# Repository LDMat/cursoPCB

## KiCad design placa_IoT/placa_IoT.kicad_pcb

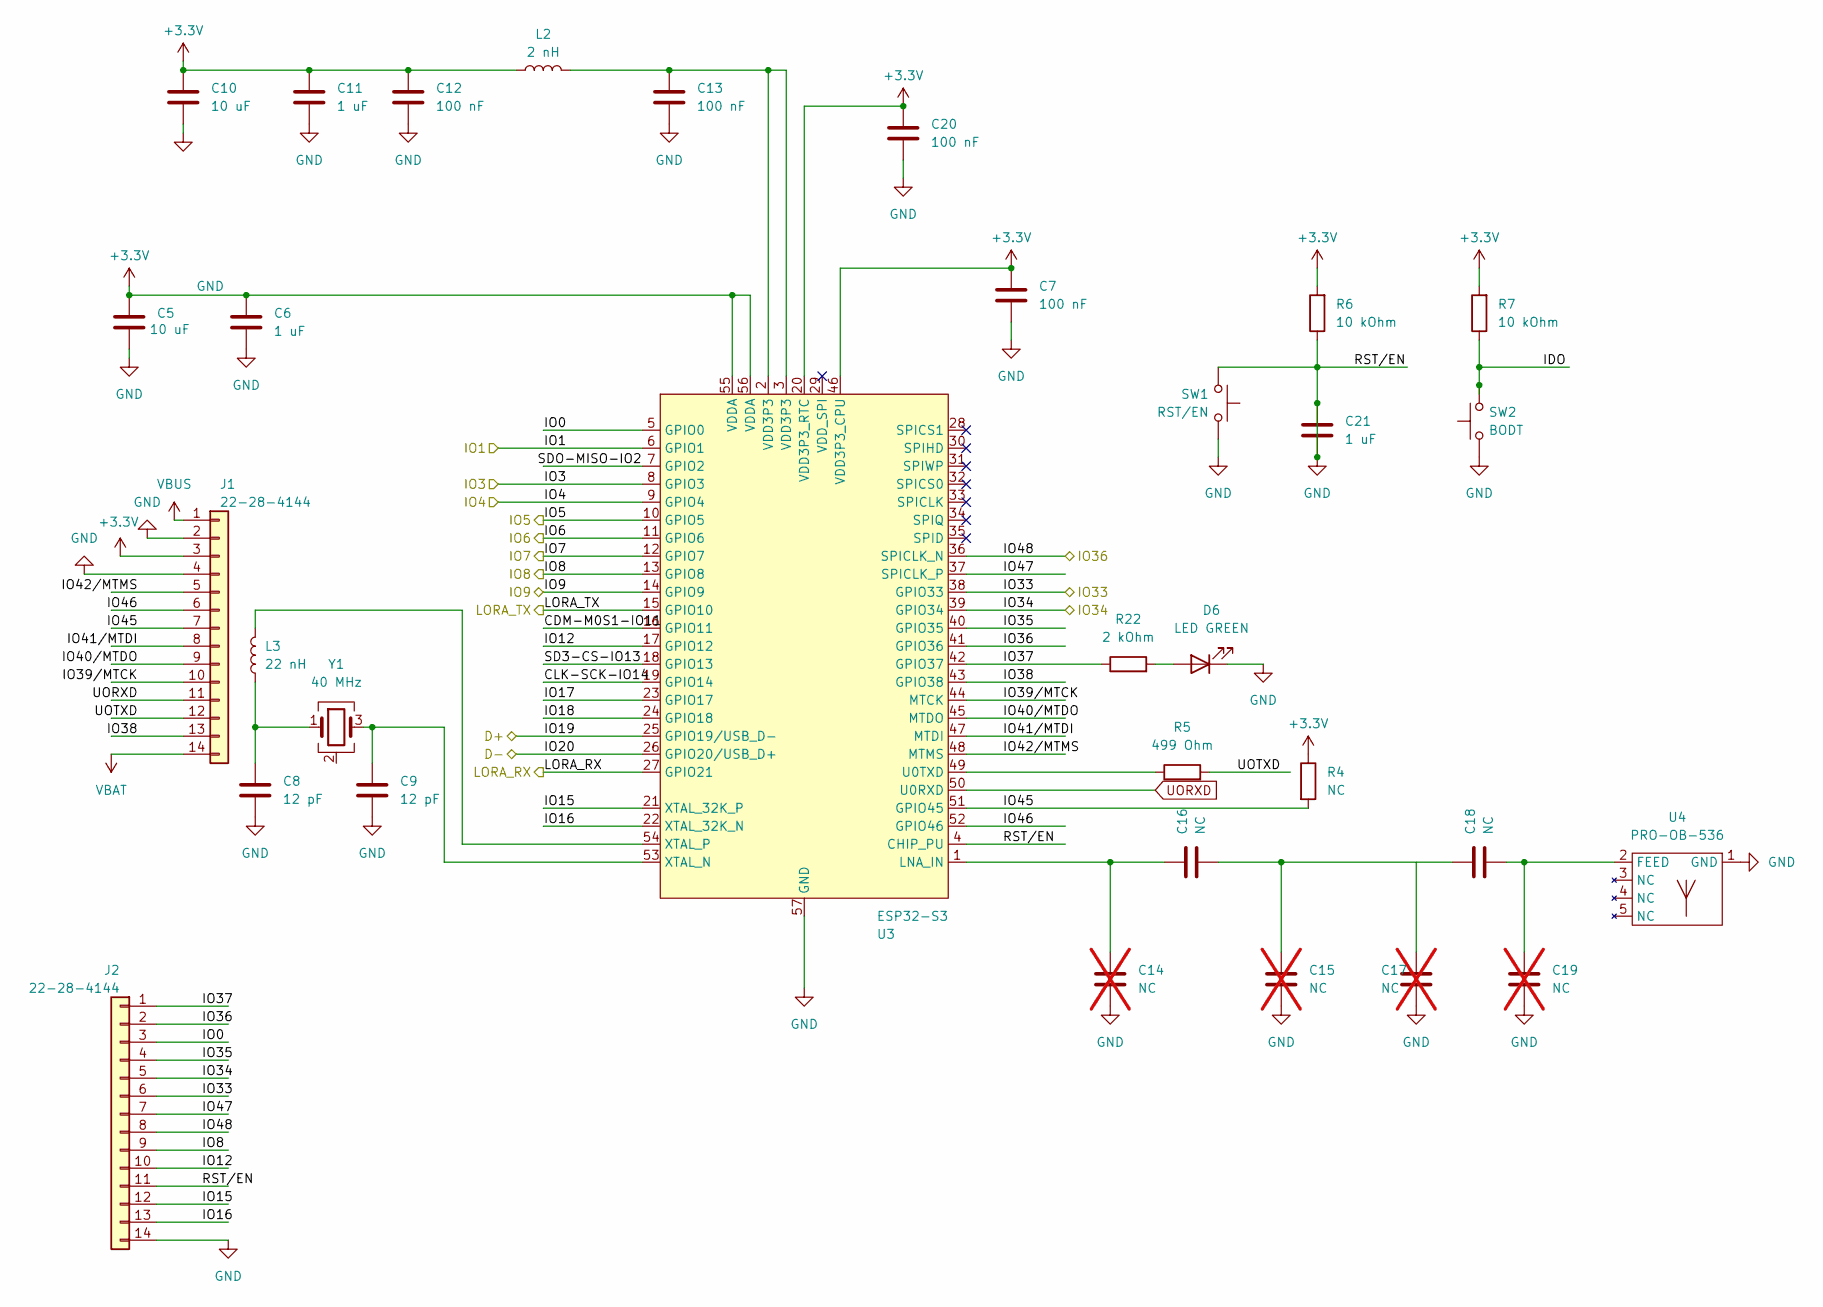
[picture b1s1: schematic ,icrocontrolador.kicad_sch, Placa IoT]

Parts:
C5, C10: 10 uF; C_0402_1005Metric
C6, C11, C21: 1 uF; C_0402_1005Metric
C7, C12, C13, C20: 100 nF; C_0402_1005Metric
C8, C9: 12 pF; C_0402_1005Metric
C14, C15, C17, C19: NC; C_0402_1005Metric; not fitted
C16, C18: NC; C_0402_1005Metric
D6: LED GREEN; LED_0402_1005Metric
J1, J2: 22-28-4144; CONN_THT_MV_PH_P2.54MM_P14
L2: 2 nH; L_0402_1005Metric
L3: 22 nH; L_0402_1005Metric
R4: NC; R_0402_1005Metric
R5: 499 Ohm; R_0402_1005Metric
R6, R7: 10 kOhm; R_0402_1005Metric
R22: 2 kOhm; R_0402_1005Metric
SW1: RST/EN; SW_Push_SPST_NO_Alps_SKRK
SW2: BODT; SW_Push_SPST_NO_Alps_SKRK
U3: ESP32-S3; QFN-56-1EP_7x7mm_P0.4mm_EP4x4mm
U4: PRO-OB-536; ANTENNA_PIFA_3D_2.4GHZ
Y1: 40 MHz; Crystal_SMD_3225-4Pin_3.2x2.5mm

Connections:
+3.3V: C5.1, C6.1, C7.1, C10.1, C11.1, C12.1, C20.1, J1.3, L2.1, R4.1, R6.2, R7.2, U3.20 (VDD3P3_RTC), U3.46 (VDD3P3_CPU), U3.55 (VDDA), U3.56 (VDDA); also elsewhere on the board
/MICROCONTROLADOR/CDM-M0S1-IO11: U3.16 (GPIO11)
/MICROCONTROLADOR/CLK-SCK-IO14: U3.19 (GPIO14)
/MICROCONTROLADOR/IDO: R7.1, SW2.2
/MICROCONTROLADOR/IO0: J2.3, U3.5 (GPIO0)
/MICROCONTROLADOR/IO1: U3.6 (GPIO1); also elsewhere on the board
/MICROCONTROLADOR/IO3: U3.8 (GPIO3); also elsewhere on the board
/MICROCONTROLADOR/IO4: U3.9 (GPIO4); also elsewhere on the board
/MICROCONTROLADOR/IO5: U3.10 (GPIO5); also elsewhere on the board
/MICROCONTROLADOR/IO6: U3.11 (GPIO6); also elsewhere on the board
/MICROCONTROLADOR/IO7: U3.12 (GPIO7)
/MICROCONTROLADOR/IO8: J2.9, U3.13 (GPIO8); also elsewhere on the board
/MICROCONTROLADOR/IO12: J2.10, U3.17 (GPIO12)
/MICROCONTROLADOR/IO15: J2.12, U3.21 (XTAL_32K_P)
/MICROCONTROLADOR/IO16: J2.13, U3.22 (XTAL_32K_N)
/MICROCONTROLADOR/IO17: U3.23 (GPIO17)
/MICROCONTROLADOR/IO18: U3.24 (GPIO18)
/MICROCONTROLADOR/IO19: U3.25 (GPIO19/USB_D-), U3.26 (GPIO20/USB_D+); also elsewhere on the board
/MICROCONTROLADOR/IO33: J2.6, U3.14 (GPIO9), U3.15 (GPIO10), U3.27 (GPIO21), U3.38 (GPIO33); also elsewhere on the board
/MICROCONTROLADOR/IO34: J2.5, U3.39 (GPIO34); also elsewhere on the board
/MICROCONTROLADOR/IO35: J2.4, U3.40 (GPIO35)
/MICROCONTROLADOR/IO36: J2.2, J2.8, U3.36 (SPICLK_N), U3.41 (GPIO36); also elsewhere on the board
/MICROCONTROLADOR/IO37: J2.1, R22.1, U3.42 (GPIO37)
/MICROCONTROLADOR/IO38: J1.13, U3.43 (GPIO38)
/MICROCONTROLADOR/IO39/MTCK: J1.10, U3.44 (MTCK)
/MICROCONTROLADOR/IO40/MTDO: J1.9, U3.45 (MTDO)
/MICROCONTROLADOR/IO41/MTDI: J1.8, U3.47 (MTDI)
/MICROCONTROLADOR/IO42/MTMS: J1.5, U3.48 (MTMS)
/MICROCONTROLADOR/IO45: J1.7, R4.2, U3.51 (GPIO45)
/MICROCONTROLADOR/IO46: J1.6, U3.52 (GPIO46)
/MICROCONTROLADOR/IO47: J2.7, U3.37 (SPICLK_P)
/MICROCONTROLADOR/SD3-CS-IO13: U3.18 (GPIO13)
/MICROCONTROLADOR/SDO-MISO-IO2: U3.7 (GPIO2)
/MICROCONTROLADOR/UOTXD: J1.12, R5.2
GND: C5.2, C6.2, C7.2, C8.2, C9.2, C10.2, C11.2, C12.2, C13.2, C14.1, C15.1, C17.1, C19.1, C20.2, C21.1, C21.2, D6.1 (K), J1.2, J1.4, J2.11, J2.14, R6.1, SW1.1, SW1.2, SW2.1, U3.4 (CHIP_PU), U3.57 (GND), U4.1 (GND); also elsewhere on the board
unnamed: C8.1, L3.1, Y1.1
unnamed: C13.1, L2.2, U3.2 (VDD3P3), U3.3 (VDD3P3)
unnamed: C15.2, C16.1, C18.2
unnamed: D6.2 (A), R22.2
unnamed: C14.2, C16.2, U3.1 (LNA_IN)
unnamed: R5.1, U3.49 (U0TXD)
unnamed: C9.1, U3.53 (XTAL_N), Y1.3
unnamed: L3.2, U3.54 (XTAL_P)
unnamed: C18.1, C19.2, U4.2 (FEED)
unnamed: Y1.2 (G), Y1.4 (G)
UORXD: J1.11, U3.50 (U0RXD)
VBAT: J1.14; also elsewhere on the board
VBUS: J1.1; also elsewhere on the board

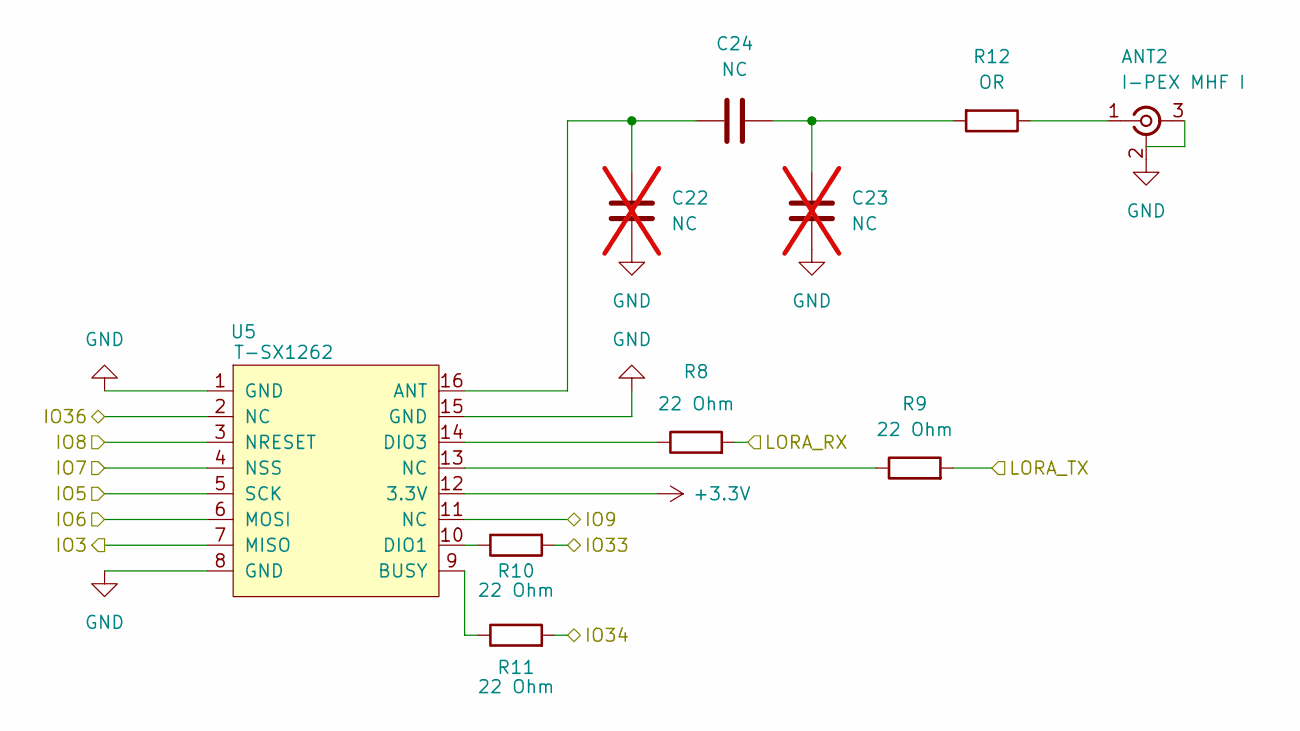
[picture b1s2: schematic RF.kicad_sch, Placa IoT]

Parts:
ANT2: I-PEX MHF I; IPEX_MHF_I
C22, C23: NC; C_0402_1005Metric; not fitted
C24: NC; C_0402_1005Metric
R8, R9, R10, R11: 22 Ohm; R_0402_1005Metric
R12: OR; R_0402_1005Metric
U5: T-SX1262; MODULE_T_SX1262

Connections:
+3.3V: U5.12 (3.3V); also elsewhere on the board
/MICROCONTROLADOR/IO3: U5.7 (MISO); also elsewhere on the board
/MICROCONTROLADOR/IO5: U5.5 (SCK); also elsewhere on the board
/MICROCONTROLADOR/IO6: U5.6 (MOSI); also elsewhere on the board
/MICROCONTROLADOR/IO8: U5.3 (NRESET); also elsewhere on the board
/MICROCONTROLADOR/IO33: R8.2, R9.2, R10.2, U5.11 (NC); also elsewhere on the board
/MICROCONTROLADOR/IO34: R11.2; also elsewhere on the board
/MICROCONTROLADOR/IO36: U5.2 (NC); also elsewhere on the board
/RF/IO7: U5.4 (NSS)
GND: ANT2.2 (Ext), C22.1, C23.1, U5.1 (GND), U5.8 (GND), U5.15 (GND); also elsewhere on the board
unnamed: ANT2.1 (In), R12.1
unnamed: C23.2, C24.1, R12.2
unnamed: R9.1, U5.13 (NC)
unnamed: C22.2, C24.2, U5.16 (ANT)
unnamed: R11.1, U5.9 (BUSY)
unnamed: R10.1, U5.10 (DIO1)
unnamed: R8.1, U5.14 (DIO3)

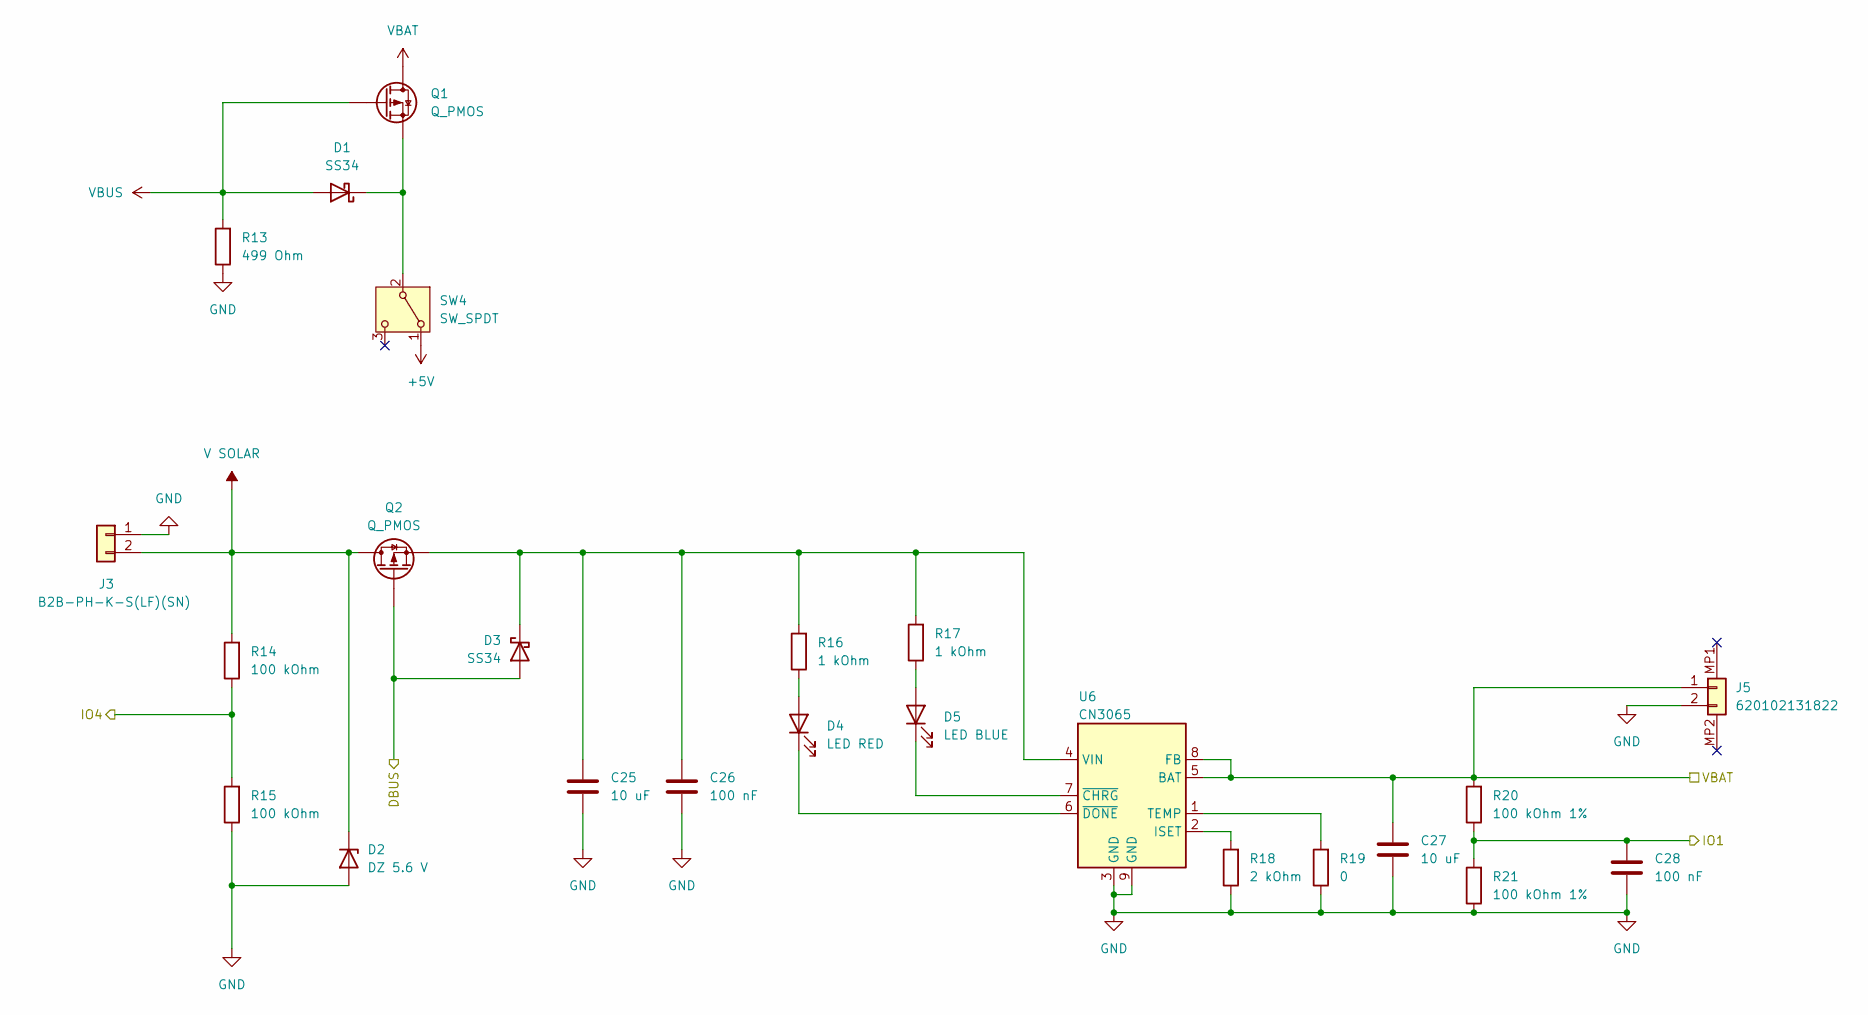
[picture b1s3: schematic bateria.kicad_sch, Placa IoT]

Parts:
C25, C27: 10 uF; C_0402_1005Metric
C26, C28: 100 nF; C_0402_1005Metric
D1, D3: SS34; D_SMA
D2: DZ 5.6 V; D_SOD-123
D4: LED RED; LED_0402_1005Metric
D5: LED BLUE; LED_0402_1005Metric
J3: B2B-PH-K-S(LF)(SN); CONN_THT_MV_JST_P2.00MM_P2
J5: 620102131822; CONN_SMT_MH_SH_P2.00MM_P2
Q1, Q2: Q_PMOS; SOT-23
R13: 499 Ohm; R_0402_1005Metric
R14, R15: 100 kOhm; R_0402_1005Metric
R16, R17: 1 kOhm; R_0402_1005Metric
R18: 2 kOhm; R_0402_1005Metric
R19: 0; R_0402_1005Metric
R20, R21: 100 kOhm 1%; R_0402_1005Metric
SW4: SW_SPDT; SW_Slide_SPDT_Angled_CK_OS102011MA1Q
U6: CN3065; DFN-8-1EP_3x3mm_P0.5mm_EP1.66x2.38mm

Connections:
+5V: SW4.1 (A); also elsewhere on the board
/BATERIA/DBUS: D3.2 (A), Q2.1 (G)
/MICROCONTROLADOR/IO1: C28.1, R20.1, R21.2; also elsewhere on the board
/MICROCONTROLADOR/IO4: R14.1, R15.2; also elsewhere on the board
GND: C25.2, C26.2, C27.2, C28.2, D2.2 (A), J3.1, J5.2, R13.1, R15.1, R18.1, R19.1, R21.1, U6.3 (GND), U6.9 (GND); also elsewhere on the board
unnamed: D1.1 (K), Q1.2 (S), SW4.2 (B)
unnamed: C25.1, C26.1, D3.1 (K), Q2.2 (S), R16.2, R17.2, U6.4 (VIN)
unnamed: D4.2 (A), R16.1
unnamed: D4.1 (K), U6.6 (~DONE)
unnamed: D5.2 (A), R17.1
unnamed: D5.1 (K), U6.7 (~CHRG)
unnamed: R18.2, U6.2 (ISET)
unnamed: R19.2, U6.1 (TEMP)
V SOLAR: D2.1 (K), J3.2, Q2.3 (D), R14.2
VBAT: C27.1, J5.1, Q1.3 (D), R20.2, U6.5 (BAT), U6.8 (FB); also elsewhere on the board
VBUS: D1.2 (A), Q1.1 (G), R13.2; also elsewhere on the board

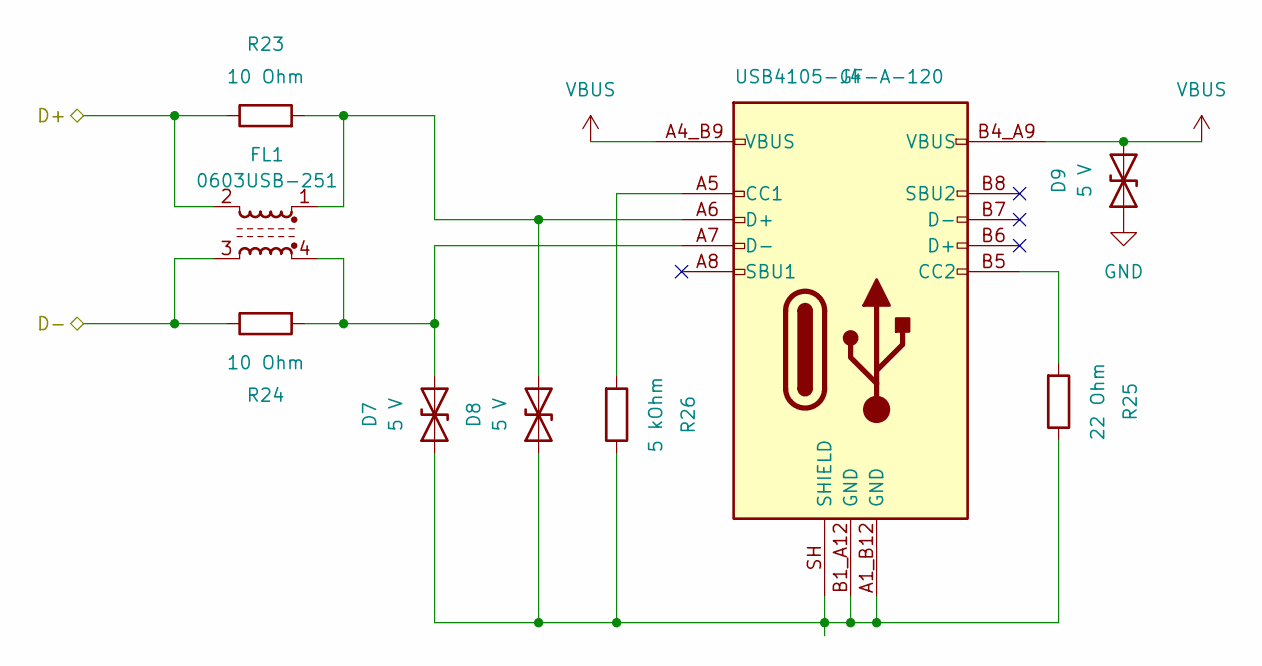
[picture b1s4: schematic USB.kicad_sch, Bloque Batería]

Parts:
D7, D8, D9: 5 V; D_SOD-882
FL1: 0603USB-251; L_CommonModeChoke_Coilcraft_0603USB
J4: USB4105-GF-A-120; CONN_SMT_RH_USBC_P0.50MM_P16
R23, R24: 10 Ohm; R_0402_1005Metric
R25: 22 Ohm; R_0402_1005Metric
R26: 5 kOhm; R_0402_1005Metric

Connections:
/MICROCONTROLADOR/IO19: FL1.2, FL1.3, R23.1, R24.1; also elsewhere on the board
GND: D9.1 (A1); also elsewhere on the board
unnamed: D7.1 (A1), D8.1 (A1), J4.A1_B12 (GND), J4.B1_A12 (GND), J4.SH (SHIELD), R25.1, R26.1
unnamed: D7.2 (A2), FL1.4, J4.A7 (D-), R24.2
unnamed: D8.2 (A2), FL1.1, J4.A6 (D+), R23.2
unnamed: J4.A5 (CC1), R26.2
unnamed: J4.B5 (CC2), R25.2
VBUS: D9.2 (A2), J4.A4_B9 (VBUS), J4.B4_A9 (VBUS); also elsewhere on the board

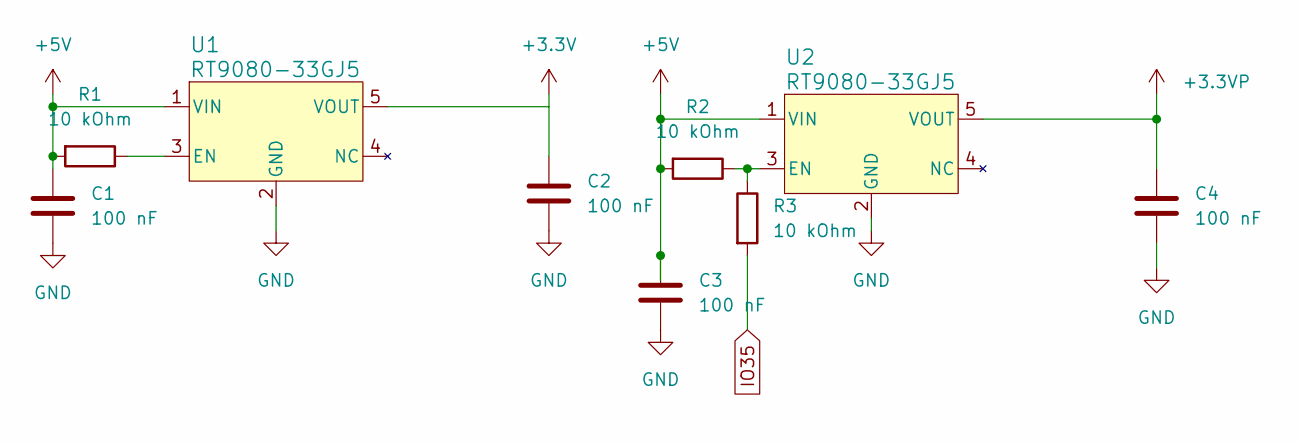
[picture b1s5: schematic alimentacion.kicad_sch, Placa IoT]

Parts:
C1, C2, C3, C4: 100 nF; C_0402_1005Metric
R1, R2, R3: 10 kOhm; R_0402_1005Metric
U1, U2: RT9080-33GJ5; TSOT-23-5_RIT

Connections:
+3.3V: C2.1; also elsewhere on the board
+3.3VP: C4.1, U2.5 (VOUT)
+5V: C1.1, C3.1, R1.2, R2.2, U1.1 (VIN), U2.1 (VIN); also elsewhere on the board
GND: C1.2, C2.2, C3.2, C4.2, U1.2 (GND), U2.2 (GND); also elsewhere on the board
IO35: R3.2
unnamed: R1.1, U1.3 (EN)
unnamed: R2.1, R3.1, U2.3 (EN)

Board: 4 copper layers, 84 parts (0 on the bottom side), 67 nets, no tracks yet.

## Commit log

2026-05-18 Primer commit
2026-05-18 Crear placa_IoT
2026-05-19 Tarea_1_Resistencia
2026-05-19 Huella resistencias add
2026-05-19 Esquemático add
2026-05-19 Alimentacion add
2026-05-19 Alimentacion def add
2026-05-19 Microprocesador in progress izq
2026-05-20 Microprocesador dcha add
2026-05-20 Microprocesador total
2026-05-20 Antena add
2026-05-20 Antena add def
2026-05-20 No conectar elementos
2026-05-20 Batería completed
2026-05-20 Diodo led micro IO37 add
2026-05-20 USB completed
2026-05-20 Falta unir pines
2026-05-20 Pines casi todos unidos
2026-05-20 Errores placa solucionados
